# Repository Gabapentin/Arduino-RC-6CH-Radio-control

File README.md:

# Arduino-RC-6CH-Radio-control

----------------------------------------------------------------------------------------------------------

| FS-CT6B |       | HK-T6A |
| ------- | :---: | ------ |
|  |  |  |    

Arduino project to upgrade cheap Hobbyking HK-T6A or Flysky FS-CT6B transmitters or any other old RC TX    

This code is based on ardutx v1.3 sketch (2014) from Patricio Reinoso www.patolin.com    

**You can see discussion on RCGroups Forum site**    
https://www.rcgroups.com/forums/showthread.php?1817699-Hobbyking-6ch-tx-arduino-computer-update

**If you want discuss this project I have already open thread on RCGroups**    
https://www.rcgroups.com/forums/showthread.php?2959179-Arduino-radio-for-HK-T6A-or-Flysky-FS-CT6B-(ArduTX-rebirth) 

----------------------------------------------------------------------------------------------------------

The code has been modified to work with SH1106 SPI 1.3" or SSD1306 SPI 0.96" OLED LCD through U8g2 library

Have been used all possible pins of ATmega328P (Arduino Nano, Pro Mini)

Every text strings has been stored in flash memory to mantain a lot of free RAM memory

----------------------------------------------------------------------------------------------------------

Added features to original Patolin code:

- 3 digital buttons input for menu (Enter/Select) (Down/Next) (Up/Previous) [previously analogs]

- Switches checking status with sound alert at power ON and display which is not in default position 

- Throttle warning with display status of switches and sound alert

- Hidden data default restoring by pressing and hold Down/Next button on power on

- Hidden calibration procedure by pressing and hold Menu/Select button on power on

- Low battery control in real time whith buzzer sound(buzzer with stand alone sound generator)

- N°2 supplementary switch, they can be configured instead of VRA or VRB pots (SWA, SWB)(Servo Direction Menu)

- Basic two channel mixer with switch activation V-Mix (Ch1/ch2)

- Basic four channels Sub Trim setting (ch1, ch2, ch3, ch4)

*************************************************************************************************************

Recommended Arduino **[Arduino IDE 1.8.2 or above](https://www.arduino.cc/en/main/software)**    
(Seems to be optimized and stable compiler. Less Flash and RAM used)

Arduino AVR Boards 1.6.18

#include <U8g2lib.h>               Using U8G2 library **[UG2 Github link](https://github.com/olikraus/U8g2_Arduino)**

#include <SPI.h>                   Arduino standard library

#include <EEPROM.h>                Arduino standard library    

### **[See Wiki pages](https://github.com/Gabapentin/Arduino-RC-6CH-Radio-control/wiki)**

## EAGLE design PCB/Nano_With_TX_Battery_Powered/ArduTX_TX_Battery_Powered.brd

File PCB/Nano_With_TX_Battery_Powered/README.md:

### **Please remember at this time It's only prototype. Will be modified!** ###    
#### This directory contains all files for Arduino Nano one layer PCB shield (60x40mm dimension)   
#### This shield will provide directly battery power to TX module like **[Multiprotocol](https://github.com/pascallanger/DIY-Multiprotocol-TX-Module)** or FRSKY/FLYSKY external module     

### **DO NOT USE this PCB for Hobbyking HK-T6A or Flysky FS-CT6B original Transmitter module**
#### NOTES:
* #### Arduino Nano must be mounted on a female header socket to permit capacitors mounting under Nano module    
* #### Maximum battery voltage is 10V (2S Lion/LiPo 8.4V is enough for long time operation)
* #### For 3S 12.6V battery voltage is necessary to modify R1 to 20K and some parameters on sketch
* #### PPM voltage is reduced from voltage divider to 2.7Vpp

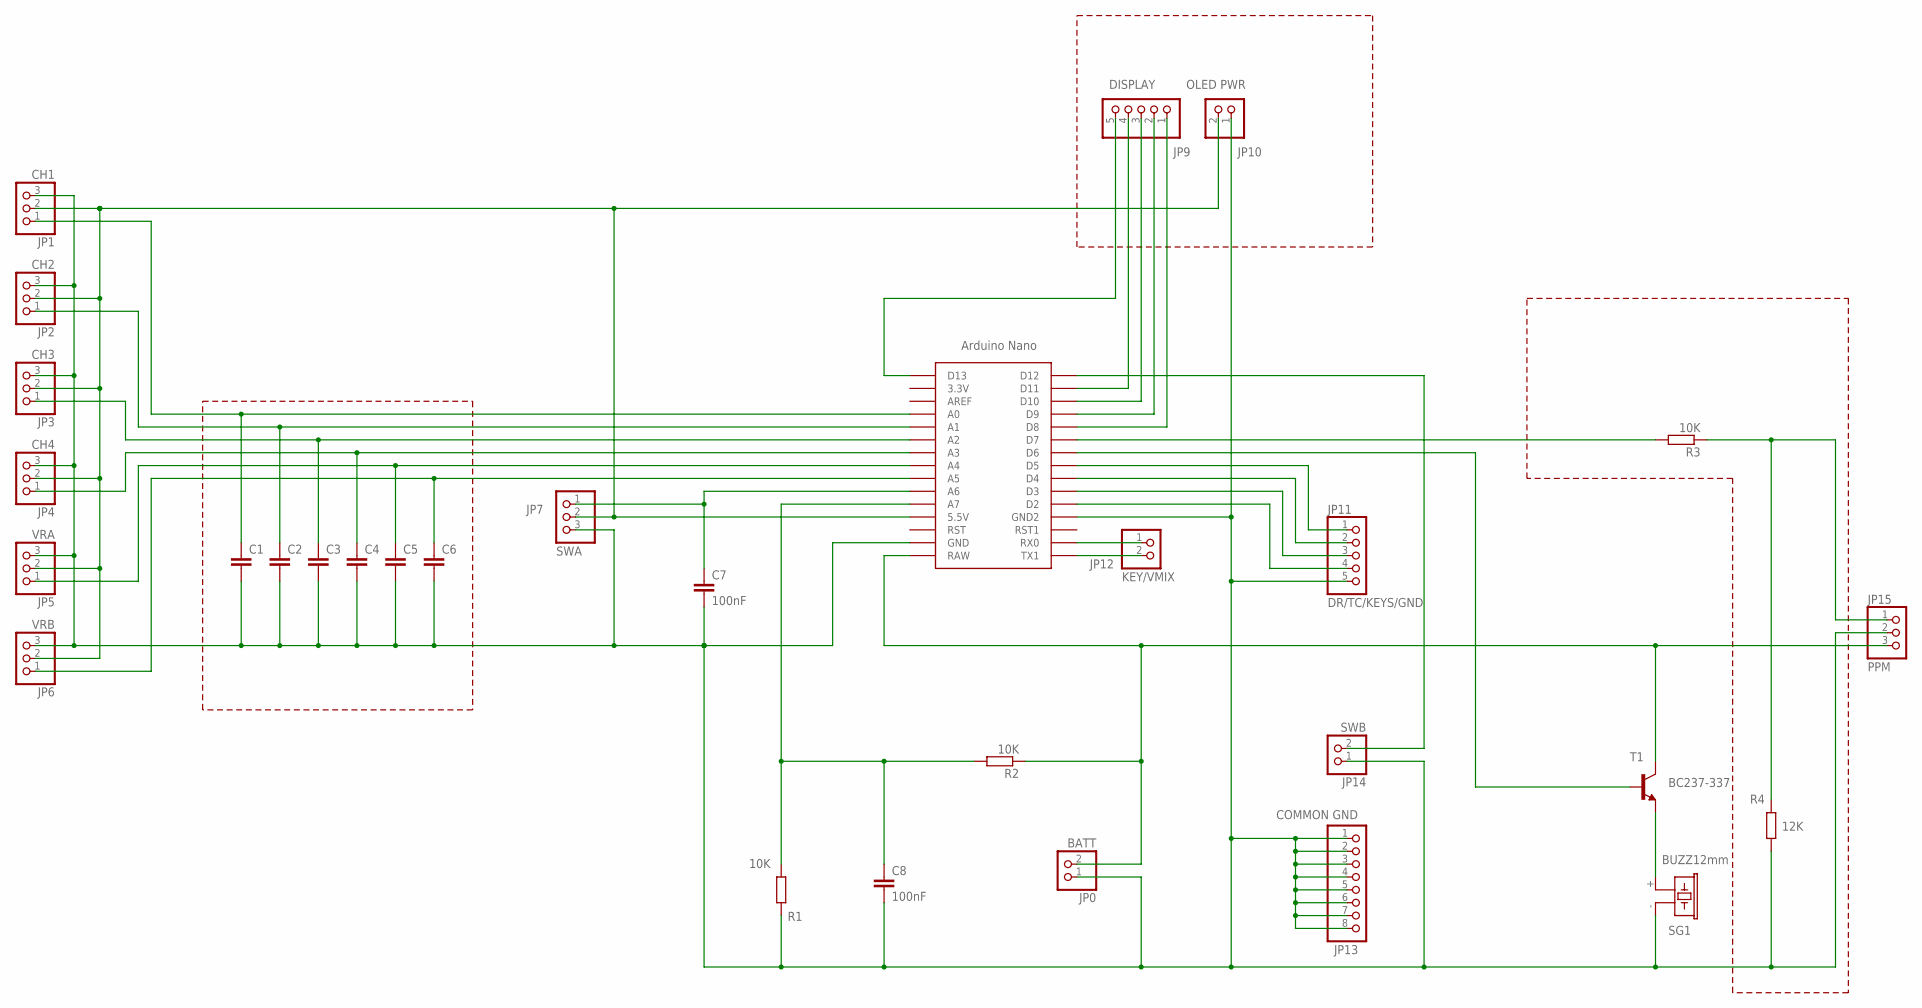
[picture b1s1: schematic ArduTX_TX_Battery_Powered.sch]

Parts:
ARDUINO-NANO: NANO
C1, C2, C3, C4, C5, C6: C-EU050-025X075; C050-025X075
C7, C8: 100nF; C050-025X075
JP0: BATT; 1X02
JP1: CH1; 1X03
JP2: CH2; 1X03
JP3: CH3; 1X03
JP4: CH4; 1X03
JP5: VRA; 1X03
JP6: VRB; 1X03
JP7: SWA; 1X03
JP9: DISPLAY; 1X05
JP10: OLED PWR; 1X02
JP11: DR/TC/KEYS/GND; 1X05
JP12: KEY/VMIX; 1X02
JP13: COMMON GND; 1X08
JP14: SWB; 1X02
JP15: PPM; 1X03
R1, R2, R3: 10K; 0207/8
R4: 12K; 0207/8
SG1: BUZZ12mm; F/CM12P
T1: BC237-337; TO92

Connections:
unnamed: ARDUINO-NANO.TX0 (TX1), JP12.2
unnamed: ARDUINO-NANO.5V (5.5V), JP1.2, JP2.2, JP3.2, JP4.2, JP5.2, JP6.2, JP7.2, JP10.2
unnamed: ARDUINO-NANO.A0, C1.1, JP1.1
unnamed: ARDUINO-NANO.A1, C2.1, JP2.1
unnamed: ARDUINO-NANO.A2, C3.1, JP3.1
unnamed: ARDUINO-NANO.A3, C4.1, JP4.1
unnamed: ARDUINO-NANO.A4, C5.1, JP5.1
unnamed: ARDUINO-NANO.A5, C6.1, JP6.1
unnamed: ARDUINO-NANO.D6, T1.2 (B)
unnamed: SG1.+ (1), T1.1 (E)
unnamed: ARDUINO-NANO.D7, R3.2
unnamed: ARDUINO-NANO.RX1 (RX0), JP12.1
unnamed: ARDUINO-NANO.D4, JP11.2
unnamed: ARDUINO-NANO.D5, JP11.1
unnamed: ARDUINO-NANO.A6, C7.1, JP7.1
unnamed: ARDUINO-NANO.D3, JP11.3
unnamed: ARDUINO-NANO.D2, JP11.4
unnamed: ARDUINO-NANO.A7, C8.1, R1.1, R2.2
unnamed: ARDUINO-NANO.D12, JP14.2
unnamed: ARDUINO-NANO.GND, ARDUINO-NANO.GND1 (GND2), C1.2, C2.2, C3.2, C4.2, C5.2, C6.2, C7.2, C8.2, JP0.1, JP1.3, JP2.3, JP3.3, JP4.3, JP5.3, JP6.3, JP7.3, JP10.1, JP11.5, JP13.1, JP13.2, JP13.3, JP13.4, JP13.5, JP13.6, JP13.7, JP13.8, JP14.1, JP15.2, R1.2, R4.1, SG1.- (2)
unnamed: ARDUINO-NANO.D10, JP9.3
unnamed: ARDUINO-NANO.D9, JP9.2
unnamed: ARDUINO-NANO.D8, JP9.1
unnamed: ARDUINO-NANO.D11, JP9.4
unnamed: ARDUINO-NANO.D13, JP9.5
unnamed: JP15.1, R3.1, R4.2
NET: ARDUINO-NANO.RAW, JP0.2, JP15.3, R2.1, T1.3 (C)

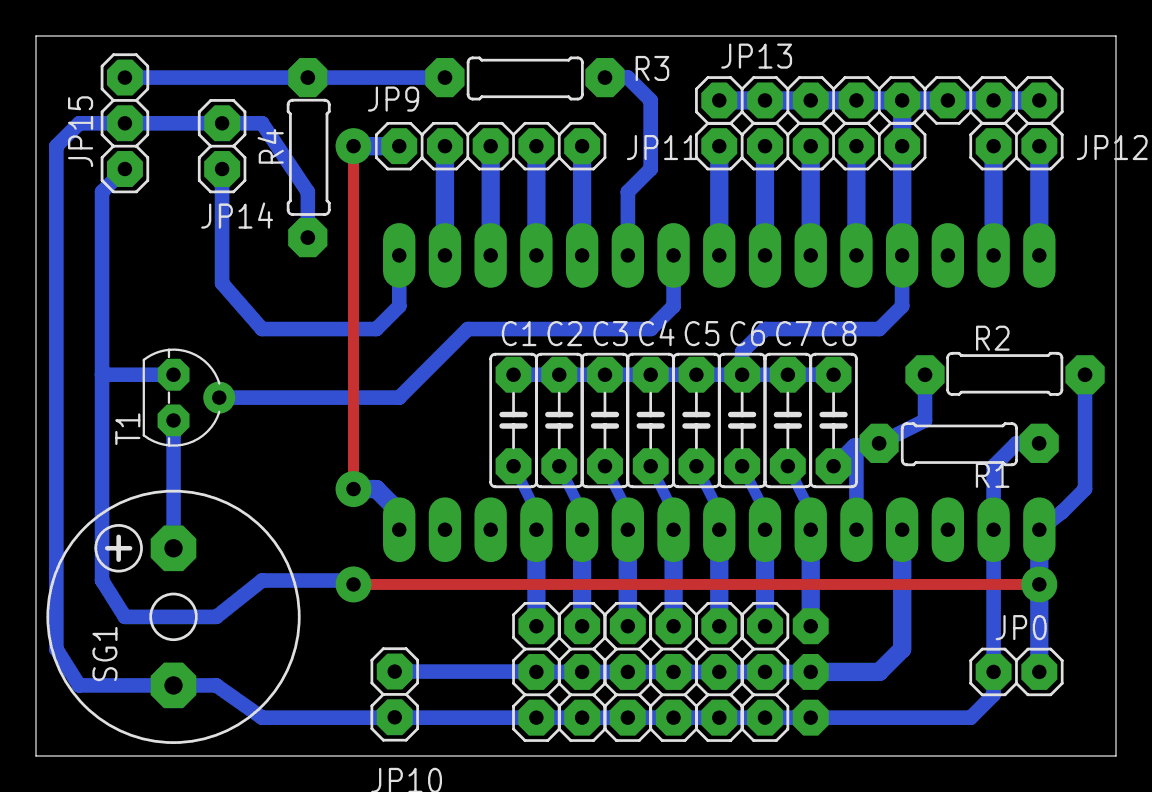
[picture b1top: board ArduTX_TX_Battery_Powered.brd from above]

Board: 2 copper layers, 60.0 x 40.0 mm, 30 parts (1 on the bottom side), 27 nets.

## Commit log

2017-09-19 Add files via upload
    Eagle schematic of Arduino TX 6CH
2017-09-26 Update Config.h
    modified comment LCD to OLED
2017-09-27 Create Clear_Eeprom
2017-09-27 Rename Clear_Eeprom to Eeprom_clear
2017-09-27 Update Eeprom_clear
2017-09-27 Rename Eeprom_clear to eeprom_clear.ino
2017-10-21 New schematic with Arduino Pro Mini
2017-10-23 Schematic update
    Schematic update to 5V power supply for original radio Turnigy/Flysky TX module
2017-11-01 Add files via upload
    Removed capacitor from pin AREF
2017-11-27 Create eagle
2018-01-17 Arduino Nano general schematic update
    - Incorrect label of Arduino TX RX pins
    - Added debounce resistors on push buttons
    - Modified piezo buzzer driving (transistor powered from battery and buzzer connected on emitter)
2018-01-21 Rename README.me to README.md
2018-01-21 Create p
2018-01-21 Added Eagle Cad Files
    Added Eagle Cad files for Arduino Nano PCB with TX module battery powered
2018-01-21 Added all files zip package
    Contain all files in this diretory
2018-01-28 Add files via upload
    Sketch file for optimize battery reading and test battery alarm through OLED display
2018-01-28 Update README.md
    ketch file for calibrate battery and testing low battery alarm with OLED display
